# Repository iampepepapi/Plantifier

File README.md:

# Plantifier

Plantifier is a real-time sensor data visualization tool designed to monitor the humidity and temperature around a plant. It helps remind you when to water the plant by providing live updates on the plant's moisture levels, as well as room temperature and humidity.

## Features

- **Real-time Data**: Continuously streams data from sensors to display live readings.
- **Visualization**: Displays data in a responsive area chart with gradient fill.
- **CSV Export**: Allows you to export the last 50 data points as a CSV file.
- **Reconnect Functionality**: Button to refresh and reconnect to the server if disconnected.

## Technologies Used

- **React**: Frontend framework for building the user interface.
- **Socket.io**: For real-time communication between the server and the client.
- **Recharts**: Library for building charts and visualizations.
- **TypeScript**: Strongly typed programming language for better code quality and maintenance.

## Getting Started

### Prerequisites

Make sure you have the following installed on your system:

- Node.js
- npm (Node Package Manager)

### Installation

1. **Clone the repository:**
   ```sh
   git clone https://github.com/your-username/plantifier.git
   cd plantifier
   ```

2. **Install the dependencies:**
   ```sh
   npm install
   ```

3. **Start the development server:**
   ```sh
   npm run dev
   ```

4. **Run the backend server:**
   Ensure your backend server that emits the sensor data via Socket.io is running. You can use the provided example or set up your own.

### Configuration

Ensure your backend server URL is correctly set in the code:
```javascript
const newSocket = io("http://localhost:3001"); // Adjust the server URL as needed
```

## Usage

Once the development server is running, open your browser and navigate to `http://localhost:3000`. You should see the live sensor data visualized in an area chart.

- **Sensor Readings**: The current moisture, temperature, and humidity levels are displayed at the top.
- **Status Indicator**: Shows the current connection status to the server.
- **Export Data**: Click the "Export Data" button to download the last 50 data points as a CSV file.
- **Reconnect**: If the connection to the server is lost, use the "Refresh Connection" button to attempt a reconnection.

## File Structure

```plaintext
plantifier/
├── public/
│   └── index.html
├── src/
│   ├── components/
│   │   ├── ui/
│   │   │   ├── button.tsx
│   │   │   ├── card.tsx
│   │   │   ├── chart.tsx
│   │   │   └── ...other components
│   ├── App.tsx
│   ├── index.tsx
│   └── ...other files
├── package.json
├── tsconfig.json
└── ...other configuration files
```

## Contributing

Contributions are welcome! Please open an issue or submit a pull request if you have any ideas or improvements.

1. Fork the Project
2. Create your Feature Branch (`git checkout -b feature/AmazingFeature`)
3. Commit your Changes (`git commit -m 'Add some AmazingFeature'`)
4. Push to the Branch (`git push origin feature/AmazingFeature`)
5. Open a Pull Request

## License

Distributed under the MIT License. See `LICENSE` for more information.

## Contact

Samuel Gonzalez - [samuel.iga03@gmail.com](samuel.iga03@gmail.com)
Patrick - [

Project Link: [https://github.com/iampepepapi/Plantifier](https://github.com/iampepepapi/Plantifier)

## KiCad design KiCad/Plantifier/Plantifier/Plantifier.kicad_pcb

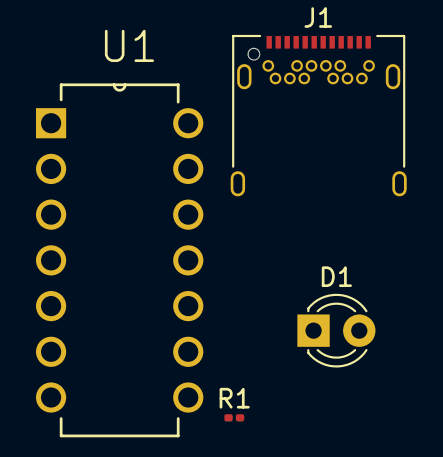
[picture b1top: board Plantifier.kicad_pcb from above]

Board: 2 copper layers, 4 parts (0 on the bottom side), 4 nets, no tracks yet.

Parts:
D1: LED; LED_D3.0mm_IRBlack
J1: 5; USB_C_Receptacle_Amphenol_12401548E4-2A
R1: 1kΩ; R_0201_0603Metric
U1: HEF4093BP_652; DIP254P762X420-14

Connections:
0: D1.1 (K), J1.A1 (GND), J1.A12 (GND), J1.B1 (GND), J1.B12 (GND), U1.7 (VSS)
+5V: J1.S1 (SHIELD), R1.1, U1.14 (VDD)
unnamed: D1.2 (A), R1.2
unnamed: J1.A4 (VBUS), J1.A9 (VBUS), J1.B4 (VBUS), J1.B9 (VBUS)

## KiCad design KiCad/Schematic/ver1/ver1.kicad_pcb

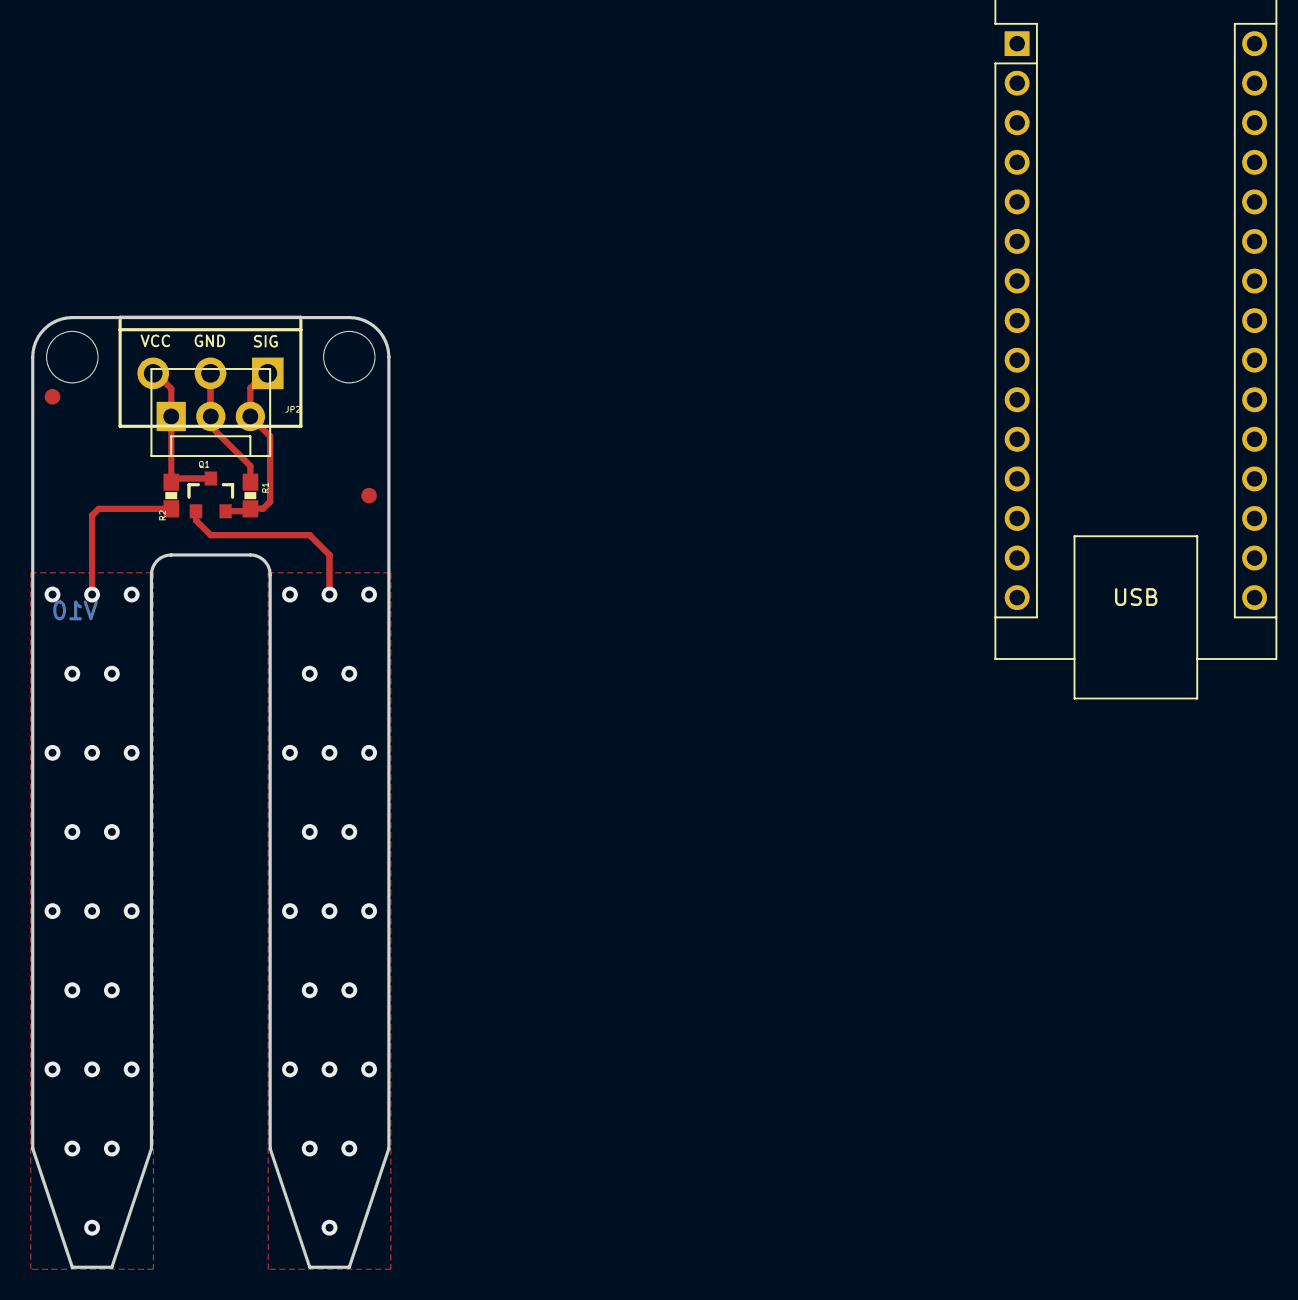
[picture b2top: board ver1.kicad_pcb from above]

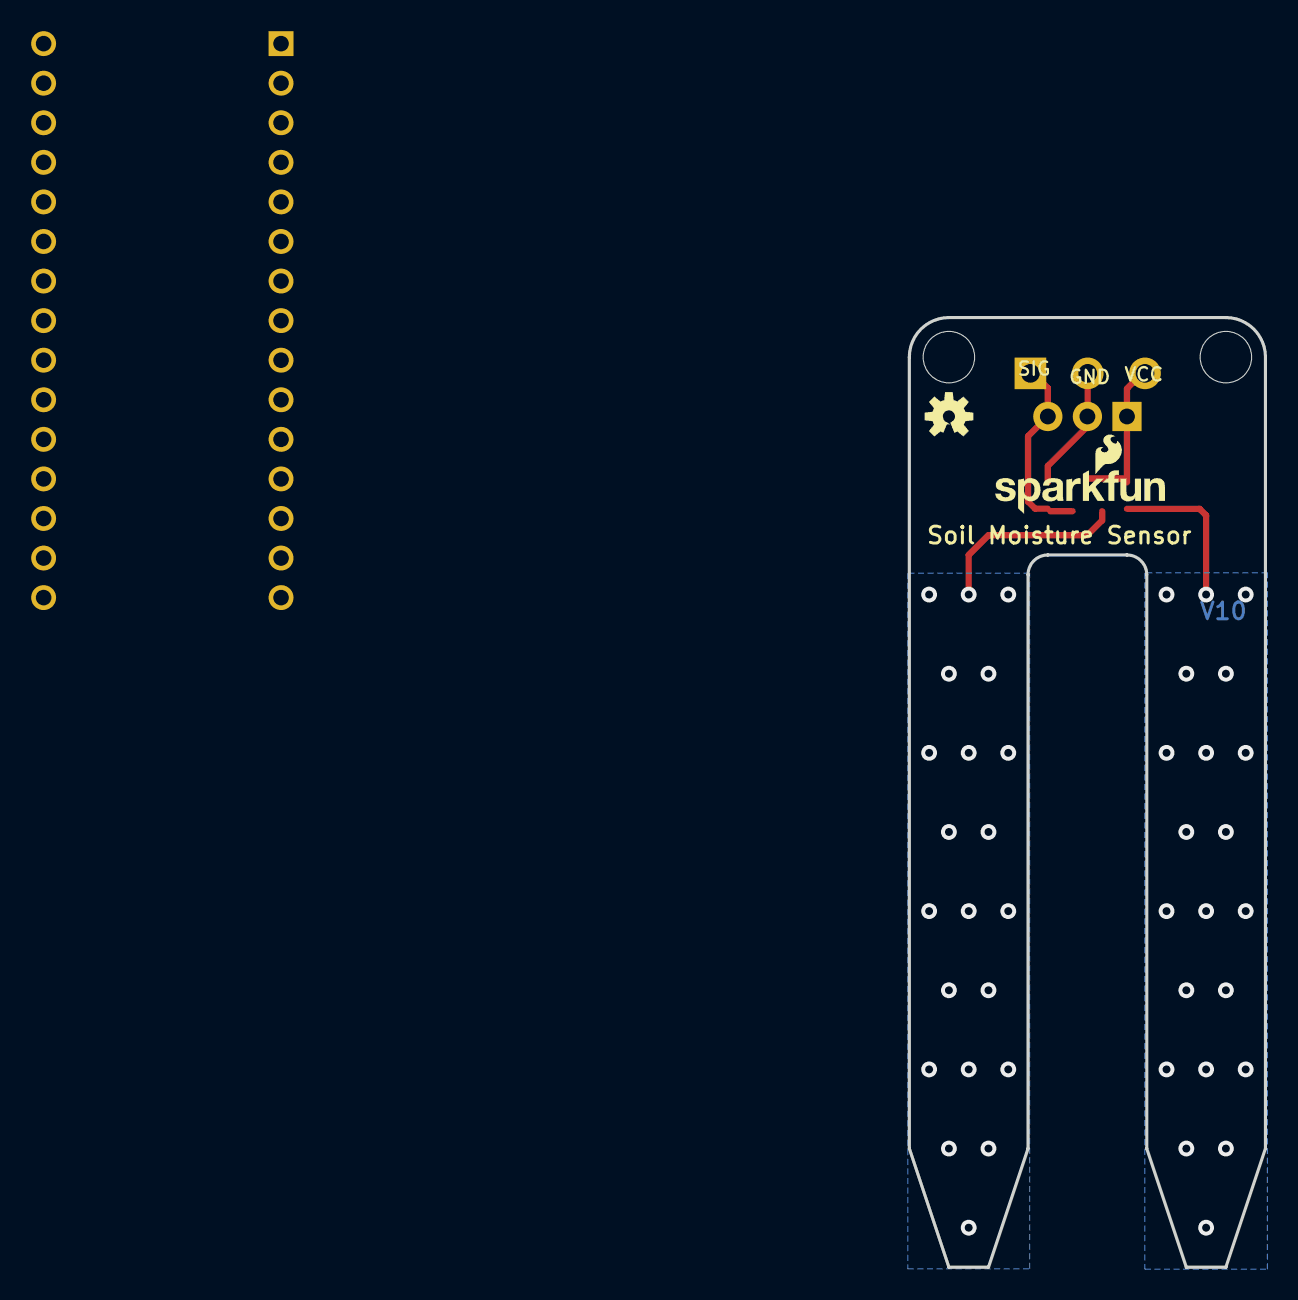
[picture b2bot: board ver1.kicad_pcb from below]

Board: 2 copper layers, 22.9 x 61.0 mm, 13 parts (2 on the bottom side), 3 nets.

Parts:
A1: Arduino_Nano_v2.x; Arduino_Nano
FID1, FID2: FIDUCIAL1X2; FIDUCIAL-1X2
FRAME1: FRAME-LETTER; CREATIVE_COMMONS
JP1: M03POLAR; MOLEX-1X3
JP2: M03SCREW_LOCK; SCREWTERMINAL-3.5MM-3_LOCK.007S
LOGO1: SFE_LOGO_NAME_FLAME.1_INCH; SFE_LOGO_NAME_FLAME_.1
LOGO2: OSHW-LOGOS; OSHW-LOGO-S
Q1: TRANSISTOR_NPNMMBT2222A; SOT23-3
R1: 10k; 0603-RES
R2: 100; 0603-RES
STANDOFF1, STANDOFF2: STAND-OFF

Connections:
/SIG: JP1.3, JP2.1, Q1.2 (E), R1.2
GND: A1.4 (GND), JP1.2, JP2.2, R1.1
VCC: JP1.1, JP2.3, Q1.3 (C), R2.2

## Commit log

2024-07-07 first 2
2024-07-07 KiCad testing
2024-07-07 Deez nuts
2024-07-07 setting up arduino
    battery source
2024-07-07 3D-models
2024-07-07 Made a folder for 3D models
2024-07-07 did somethings...
2024-07-08 SparkFun - Schematic and Gerber file working.
2024-07-08 Mild Setup for Arduino on VSCode + More Schematic
2024-07-14 Arduino setup ready fArduino -> pPlantifier
2024-07-14 Humidity Sensor DHT Library Arduino | Working
    this took waaaay too long
2024-07-29 a lot
2024-07-30 did some work
2024-07-30 Update README.md - pepe
2024-07-30 fixed page.tsx + csv export
2024-08-01 Fritzing & Next.JS
    # Fritzing
    - breadboard wiring
    - schematic
    [ ] - Need to fix KiCad library moisture sensor issues :exclamation:
    # Next.JS
    - Refactored the home layout page
2024-08-04 plantifier stuff
    yes
2024-08-04 test

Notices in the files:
parts and their libraries:
https://creativecommons.org/licenses/by-sa/4.0
Released under the Creative Commons Attribution Share-Alike 4.0 License
